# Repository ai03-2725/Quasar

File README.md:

# Quasar
A replacement controller for the IBM Model M Space Saving keyboard

#### In light of recent claims that I am 100% liable for any of my open source PCBs, I am adding this disclaimer.
#### I provide these PCBs as a reference for designing keyboard PCBs. Using them within your projects will require a will to do research of one's own and to learn the workings of them, potentially fixing issues if they exist.
# I provide these PCBs without liability and without any guarantees regarding functionality, as expressed in the MIT license under which all of these PCBs are licensed.

### Features 
* ATmega32u4-based
* USB-B

### Credits
* Antonizoon's [Model M USB controller research](https://github.com/antonizoon/antonizoon.github.io/wiki/IBM-Model-M-USB-Controller)
* Phosphorglow's [SSK matrix reverse engineering](https://deskthority.net/viewtopic.php?t=8149)
* 9595's [Model M controller dimensions](http://ps-2.kev009.com/ohlandl/keyboard/Keyboard.html)
* Lmorchard's [Model M USB controller research](http://blog.lmorchard.com/2016/02/21/modelm-controller/#secrets-of-2kro-matrices)

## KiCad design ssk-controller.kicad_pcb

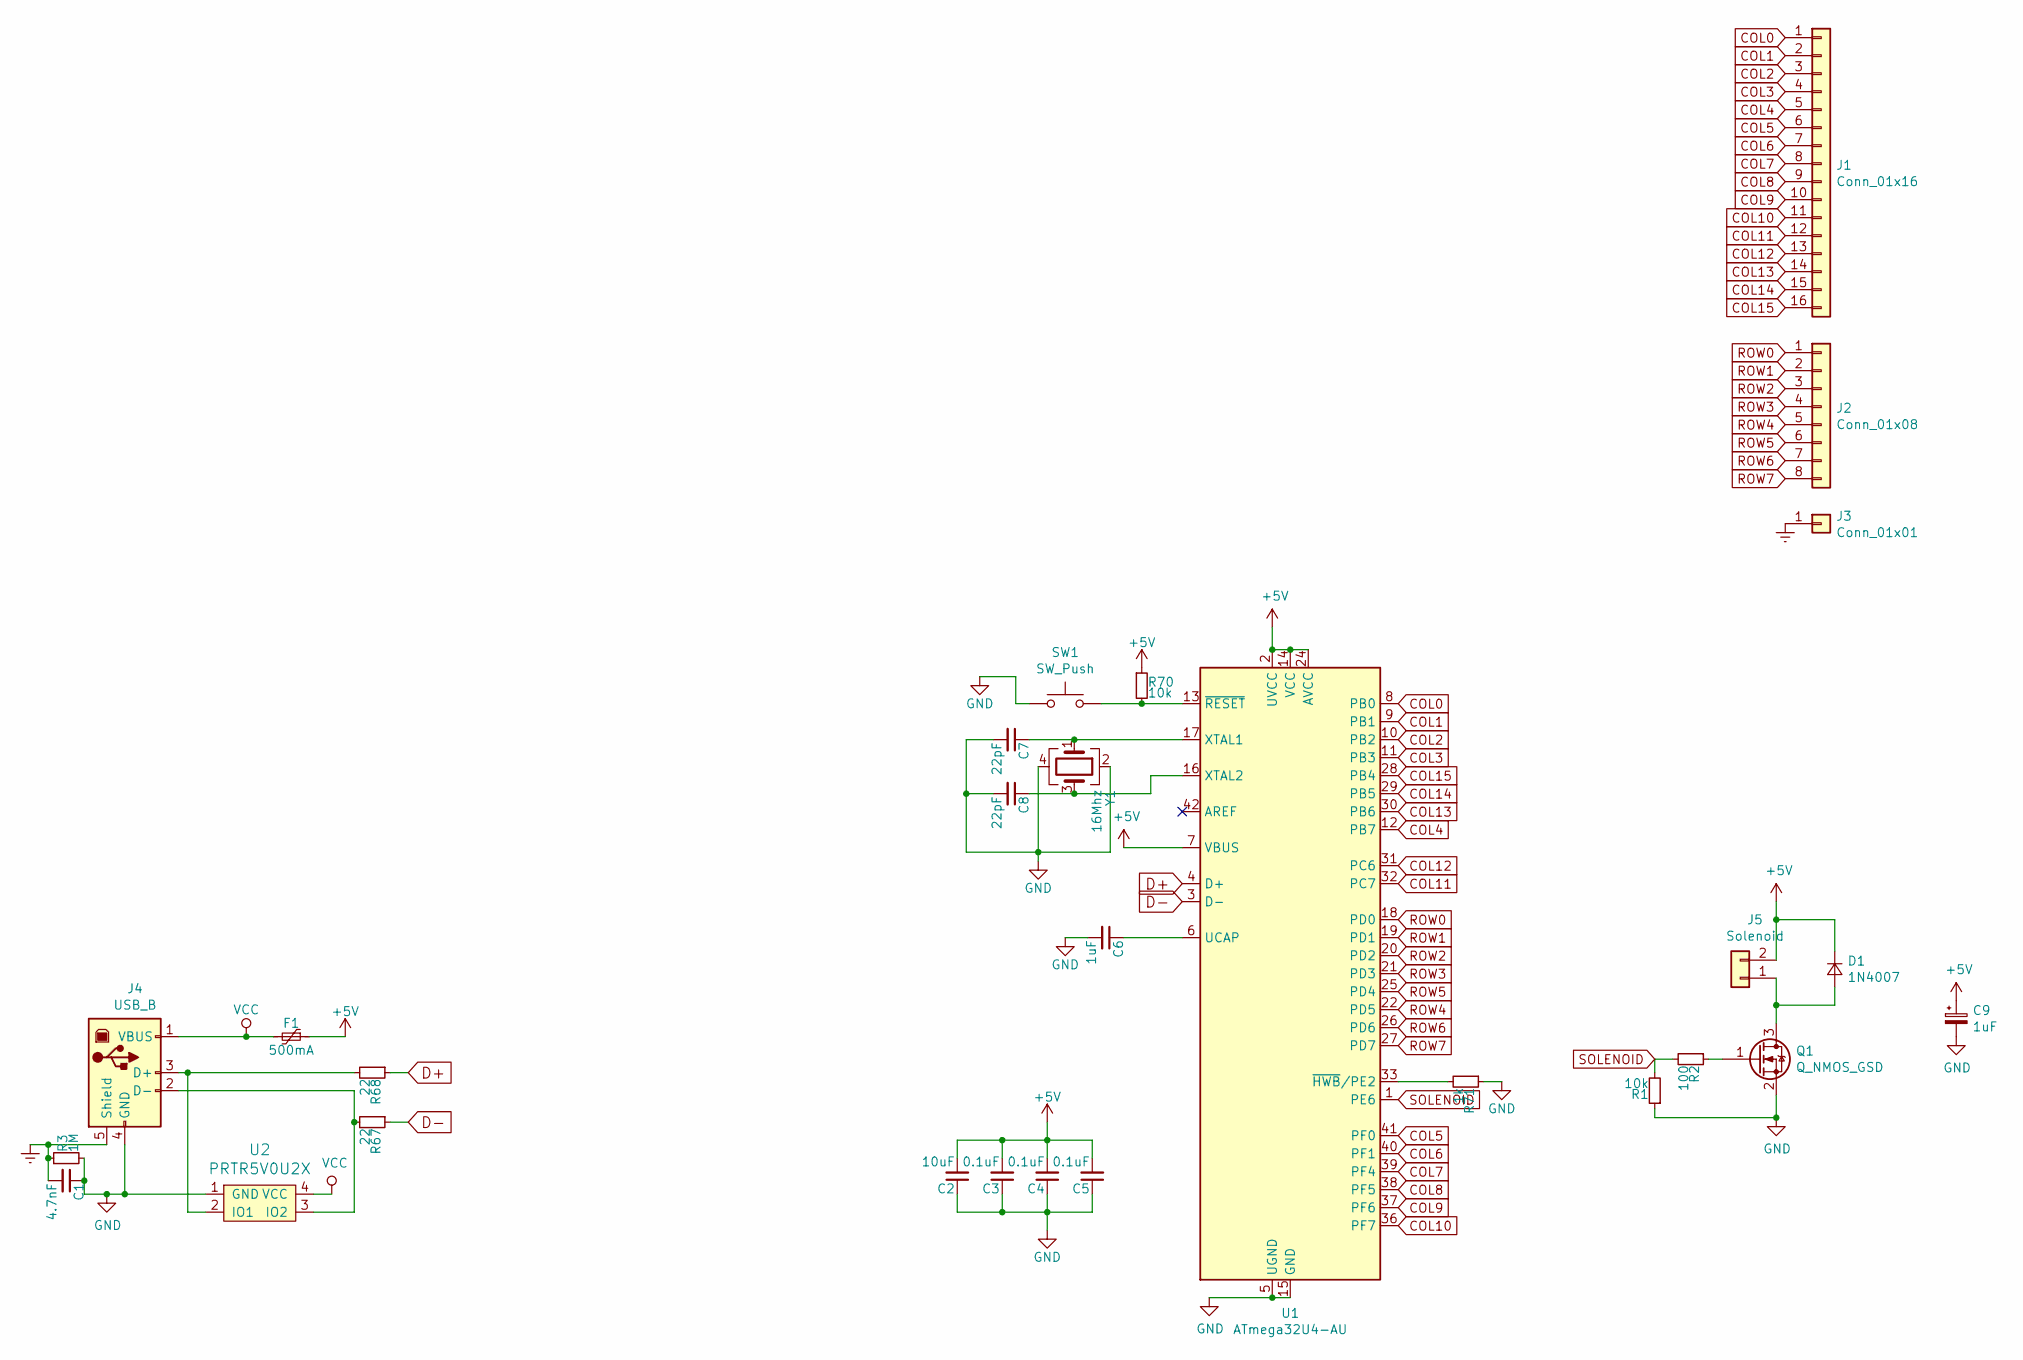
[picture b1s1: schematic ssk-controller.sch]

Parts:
C1: 4.7nF; C_0805_2012Metric
C2: 10uF; C_0805_2012Metric
C3, C4, C5: 0.1uF; C_0805_2012Metric
C6: 1uF; C_0805_2012Metric
C7, C8: 22pF; C_0805_2012Metric
C9: 1uF; CP_EIA-3216-18_Kemet-A
D1: 1N4007; D_SOD-123
F1: 500mA; Fuse_1206_3216Metric
J1: Conn_01x16; PinHeader_1x16_P2.54mm_Vertical
J2: Conn_01x08; PinHeader_1x08_P2.54mm_Vertical
J3: Conn_01x01; PinHeader_1x01_P2.54mm_Vertical
J4: USB_B; TE-292304-2
J5: Solenoid; PinHeader_1x02_P2.54mm_Vertical
Q1: Q_NMOS_GSD; SOT-23
R1, R70: 10k; R_0805_2012Metric
R2: 100; R_0805_2012Metric
R3: 1M; R_0805_2012Metric
R67, R68: 22; R_0805_2012Metric
R71: 1k; R_0805_2012Metric
SW1: SW_Push; SKQG-1155865
U1: ATmega32U4-AU; TQFP-44_10x10mm_P0.8mm
U2: PRTR5V0U2X; SOT143B
Y1: 16Mhz; Crystal_SMD_3225-4Pin_3.2x2.5mm

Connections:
+5V: C2.2, C3.2, C4.2, C5.2, C9.1, D1.1 (K), F1.1, J5.2, R70.1, U1.2 (UVCC), U1.7 (VBUS), U1.14 (VCC), U1.24 (AVCC), U1.34 (VCC), U1.44 (AVCC)
COL0: J1.1, U1.8 (PB0)
COL1: J1.2, U1.9 (PB1)
COL2: J1.3, U1.10 (PB2)
COL3: J1.4, U1.11 (PB3)
COL4: J1.5, U1.12 (PB7)
COL5: J1.6, U1.41 (PF0)
COL6: J1.7, U1.40 (PF1)
COL7: J1.8, U1.39 (PF4)
COL8: J1.9, U1.38 (PF5)
COL9: J1.10, U1.37 (PF6)
COL10: J1.11, U1.36 (PF7)
COL11: J1.12, U1.32 (PC7)
COL12: J1.13, U1.31 (PC6)
COL13: J1.14, U1.30 (PB6)
COL14: J1.15, U1.29 (PB5)
COL15: J1.16, U1.28 (PB4)
D+: R68.1, U1.4 (D+)
D-: R67.1, U1.3 (D-)
Earth: C1.2, J3.1, J4.5 (Shield), R3.1
GND: C1.1, C2.1, C3.1, C4.1, C5.1, C6.2, C7.2, C8.2, C9.2, J4.4 (GND), Q1.2 (S), R1.1, R3.2, R71.1, SW1.1, U1.5 (UGND), U1.15 (GND), U1.23 (GND), U1.35 (GND), U1.43 (GND), U2.1 (GND), Y1.2, Y1.4
unnamed: C6.1, U1.6 (UCAP)
unnamed: C7.1, U1.17 (XTAL1), Y1.1
unnamed: C8.1, U1.16 (XTAL2), Y1.3
unnamed: D1.2 (A), J5.1, Q1.3 (D)
unnamed: J4.2 (D-), R67.2, U2.3 (IO2)
unnamed: J4.3 (D+), R68.2, U2.2 (IO1)
unnamed: Q1.1 (G), R2.1
unnamed: R70.2, SW1.2, U1.13 (~RESET)
unnamed: R71.2, U1.33 (~HWB~/PE2)
ROW0: J2.1, U1.18 (PD0)
ROW1: J2.2, U1.19 (PD1)
ROW2: J2.3, U1.20 (PD2)
ROW3: J2.4, U1.21 (PD3)
ROW4: J2.5, U1.22 (PD5)
ROW5: J2.6, U1.25 (PD4)
ROW6: J2.7, U1.26 (PD6)
ROW7: J2.8, U1.27 (PD7)
SOLENOID: R1.2, R2.2, U1.1 (PE6)
VCC: F1.2, J4.1 (VBUS), U2.4 (VCC)

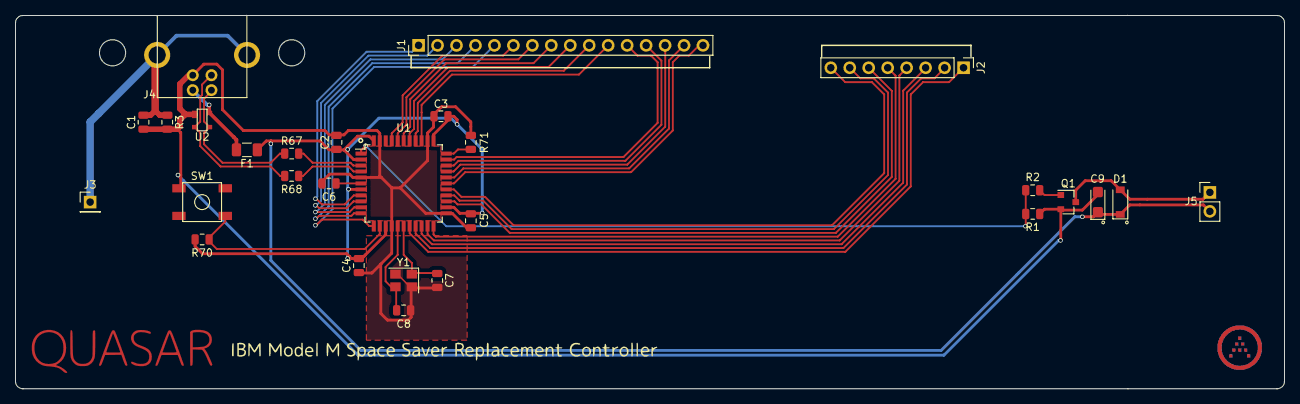
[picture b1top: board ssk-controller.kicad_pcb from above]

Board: 2 copper layers, 170.0 x 50.0 mm, 28 parts (0 on the bottom side), 40 nets.

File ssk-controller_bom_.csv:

Component,Description,Part,References,Value,Footprint,Quantity Per PCB,Datasheet
1,"Unpolarized capacitor, small symbol",C_Small,C3 C4 C5,0.1uF,C_0805_2012Metric,3,
2,"Unpolarized capacitor, small symbol",C_Small,C2,10uF,C_0805_2012Metric,1,
3,"Unpolarized capacitor, small symbol",C_Small,C6,1uF,C_0805_2012Metric,1,
4,"Unpolarized capacitor, small symbol",C_Small,C7 C8,22pF,C_0805_2012Metric,2,
5,"Unpolarized capacitor, small symbol",C_Small,C1,4.7nF,C_0805_2012Metric,1,
6,"Diode, small symbol",D_Small,D1,1N4007,D_SOD-123,1,~
7,"Resettable fuse, polymeric positive temperature coefficient, small symbol",Polyfuse_Small,F1,500mA,Fuse_1206_3216Metric,1,
8,"Generic connector, single row, 01x01, script generated (kicad-library-utils/schlib/autogen/connector/)",Conn_01x01,J3,Conn_01x01,PinHeader_1x01_P2.54mm_Vertical,1,~
9,"Generic connector, single row, 01x08, script generated (kicad-library-utils/schlib/autogen/connector/)",Conn_01x08,J2,Conn_01x08,PinHeader_1x08_P2.54mm_Vertical,1,~
10,"Generic connector, single row, 01x16, script generated (kicad-library-utils/schlib/autogen/connector/)",Conn_01x16,J1,Conn_01x16,PinHeader_1x16_P2.54mm_Vertical,1,~
11,"Generic connector, single row, 01x02, script generated (kicad-library-utils/schlib/autogen/connector/)",Conn_01x02,J5,Solenoid,PinHeader_1x02_P2.54mm_Vertical,1,~
12,"Generic connector, single row, 01x03, script generated (kicad-library-utils/schlib/autogen/connector/)",Conn_01x03,J6,Solenoid_Signal,JST-SR-3,1,~
13,USB Type B connector,USB_B,J4,USB_B,TE-292304-2,1, ~
14,"N-MOSFET transistor, gate/source/drain",Q_NMOS_GSD,Q1,Q_NMOS_GSD,SOT-23,1,~
15,"Resistor, small symbol",R_Small,R2,100,R_0805_2012Metric,1,
16,"Resistor, small symbol",R_Small,R70,10k,R_0805_2012Metric,1,
17,"Resistor, small symbol",R_Small,R1 R3,1M,R_0805_2012Metric,2,
18,"Resistor, small symbol",R_Small,R71,1k,R_0805_2012Metric,1,
19,"Resistor, small symbol",R_Small,R67 R68,22,R_0805_2012Metric,2,
20,"Push button switch, generic, two pins",SW_Push,SW1,SW_Push,SKQG-1155865,1,
21,"16MHz, 16kB Flash, 1.25kB SRAM, 512B EEPROM, USB 2.0, TQFP-44",ATmega32U4-AU,U1,ATmega32U4-AU,TQFP-44_10x10mm_P0.8mm,1,http://ww1.microchip.com/downloads/en/DeviceDoc/Atmel-7766-8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
22,,PRTR5V0U2X,U2,PRTR5V0U2X,SOT143B,1,
23,"Four pin crystal, GND on pins 2 and 4",Crystal_GND24,Y1,16Mhz,Crystal_SMD_3225-4Pin_3.2x2.5mm,1,





Component Groups:,23
Component Count:,28
Fitted Components:,28
Number of PCBs:,1
Total components:,28
Schematic Version:,
Schematic Date:,
BoM Date:,3/31/2020 9:19:48 AM
Schematic Source:,C:\Users\Ryota Goto\Documents\GitHub\Quasar\ssk-controller.sch
KiCad Version:,Eeschema (5.1.4)-1

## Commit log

2019-03-13 Begin project
2019-03-13 Finish board
2019-03-13 Start writing readme
2019-03-13 Insert render
2019-03-13 Update gerber, minor trace fix
2019-03-13 Release 1.0
2019-05-27 New gerbers for USB B
2019-05-27 Tune silkscreen
2020-03-22 Add solenoid support and better ESD handling
2020-03-22 Cleanup traces
2020-03-23 Update to 2.0 gerbers
2020-03-31 Add both 9V and 5V solenoid compat
2020-03-31 Position and bom files
2020-09-29 Create JLC files
2020-09-29 Remove JST header, focus on 5V direct solenoid
